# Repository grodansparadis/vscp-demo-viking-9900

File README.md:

# vscp-demo-viking-9900
PLC interface for Viking 9900 pellets burner to CAN4VSCP Beijing and Accra modules

**Note!** This is still a prototype.

## PCB's

---

Part of the [VSCP Project](https://www.vscp.org).

Copyright 2021-2022 © Åke Hedman, (Grodans Paradis AB)[https://www.grodansparadis.com]

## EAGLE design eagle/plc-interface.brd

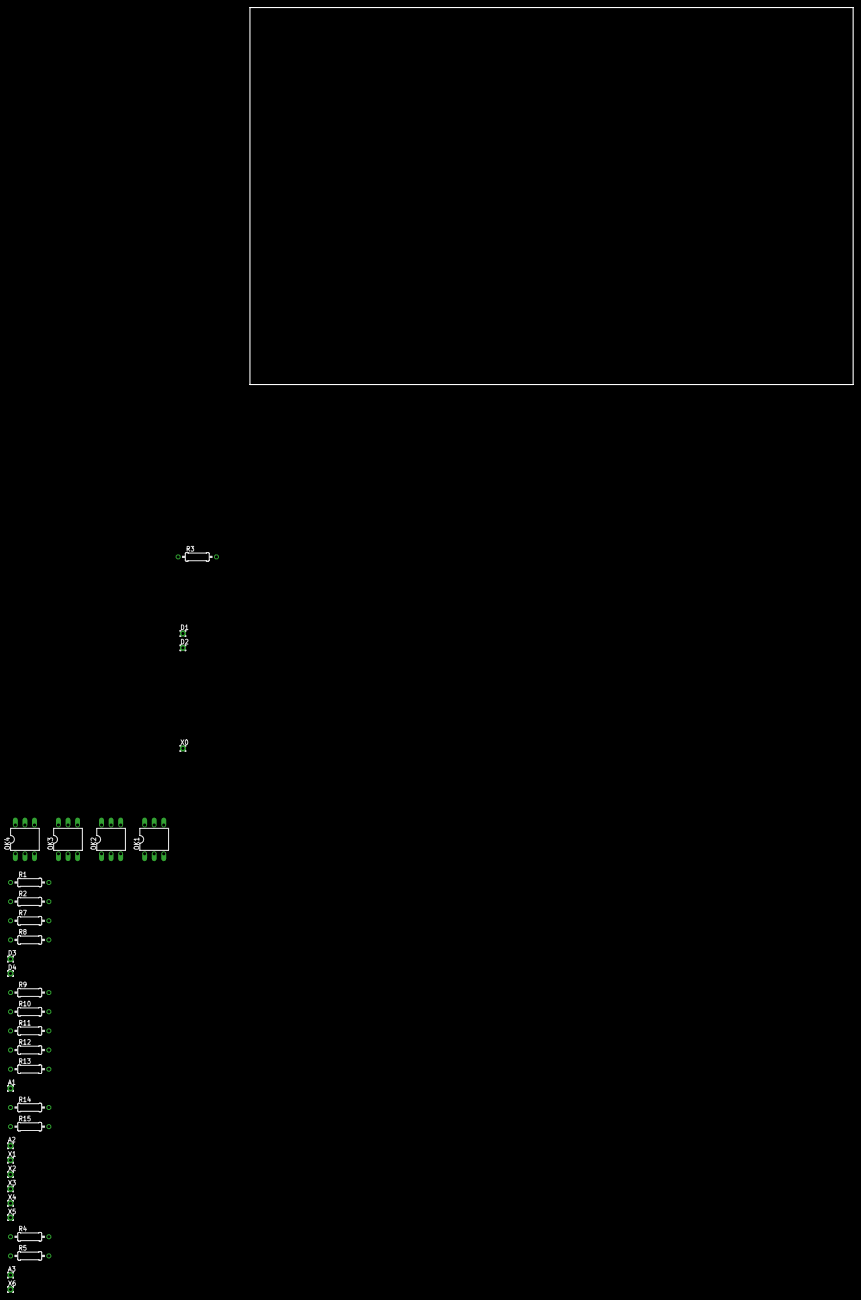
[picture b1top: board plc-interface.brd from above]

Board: 2 copper layers, 160.0 x 100.0 mm, 32 parts (0 on the bottom side), 17 nets, no tracks yet.

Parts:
A1, A2, A3: 1,6/0,8
D1, D2, D3, D4: 1,6/0,8
OK1, OK2, OK3, OK4: CNY17F; DIL06
R1, R2, R7, R8: 2k4; 0207/10
R3, R4, R5, R9, R10, R11, R12, R13, R14, R15: 10k; 0207/10
X0, X1, X2, X3, X4, X5, X6: 1,6/0,8

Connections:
+5V: R3.2, R9.2, R10.2, R11.2
GND: OK1.2, OK1.4, OK2.2, OK2.4, OK3.2, OK3.4, OK4.2, OK4.4, R5.1, R13.1
unnamed: OK1.1, R8.1
unnamed: OK4.1, R1.1
unnamed: D2.1, R7.2
unnamed: D3.1, R2.2
unnamed: D4.1, R1.2
unnamed: OK1.5, R3.1, X0.1
unnamed: OK2.5, R9.1, X1.1
unnamed: OK3.5, X2.1
unnamed: OK4.5, R11.1, X3.1
unnamed: R12.1, R13.2, X4.1
unnamed: A1.1, R12.2
unnamed: R14.1, R15.2, X5.1
unnamed: A2.1, R14.2
unnamed: R4.1, R5.2, X6.1
unnamed: A3.1, R4.2

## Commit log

2021-05-21 Added eagle folder
2021-05-21 Rev A
2021-05-25 Added gerbers
2021-05-25 Added info
2021-05-25 Added copyright info
2022-02-03 Updated copyright
